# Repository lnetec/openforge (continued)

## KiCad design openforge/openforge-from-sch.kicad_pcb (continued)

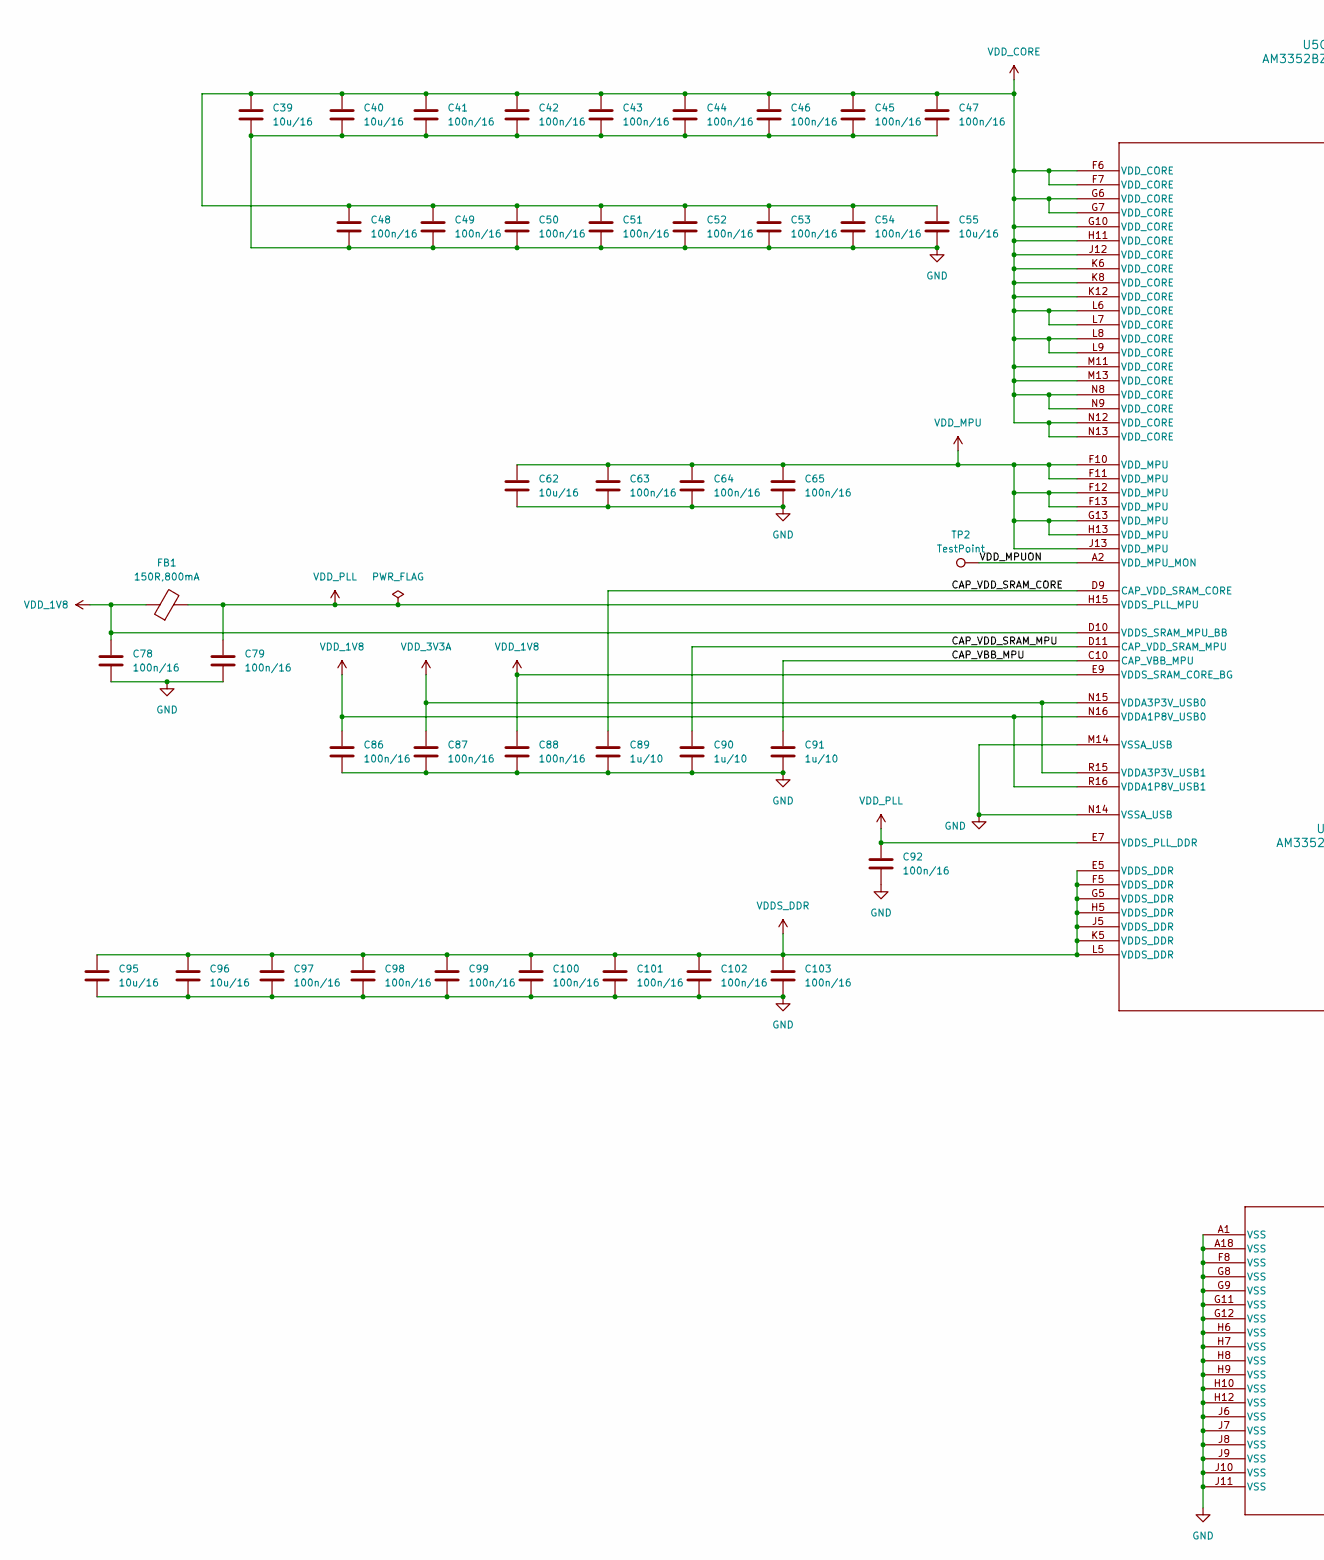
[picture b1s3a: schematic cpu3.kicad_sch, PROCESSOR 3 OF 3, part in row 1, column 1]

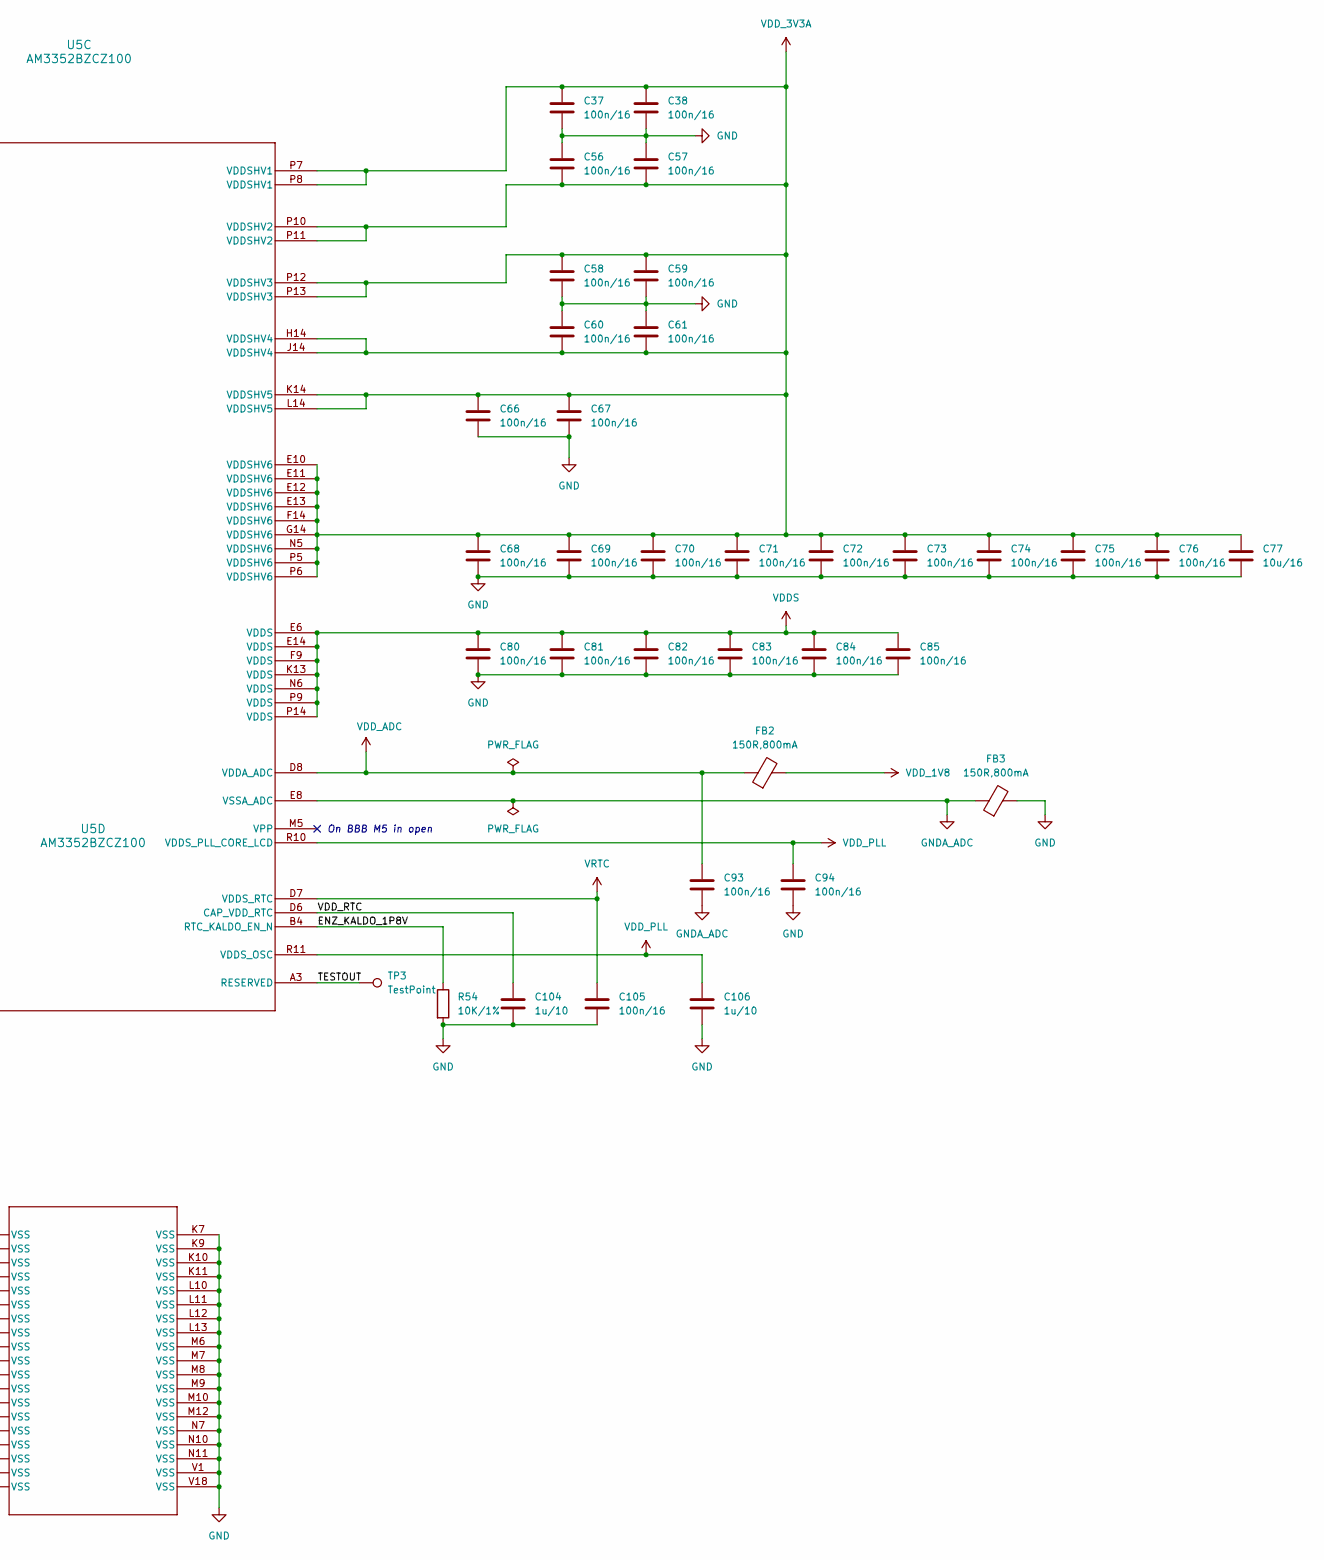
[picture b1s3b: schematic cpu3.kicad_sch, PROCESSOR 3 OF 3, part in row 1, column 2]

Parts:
C37, C38, C41, C42, C43, C44, C45, C46, C47, C48, C49, C50, C51, C52, C53, C54, C56, C57, C58, C59, C60, C61, C63, C64, C65, C66, C67, C68, C69, C70, C71, C72, C73, C74, C75, C76, C78, C79, C80, C81, C82, C83, C84, C85, C86, C87, C88, C92, C93, C94, C97, C98, C99, C100, C101, C102, C103, C105: 100n/16; C_0402_1005Metric
C39, C40, C55, C62, C95, C96: 10u/16; C_0805_2012Metric
C77: 10u/16; C_0402_1005Metric
C89, C90, C91, C104, C106: 1u/10; C_0402_1005Metric
FB1, FB2, FB3: 150R,800mA; L_0805_2012Metric
R54: 10K/1%; R_0402_1005Metric
TP2, TP3: TestPoint; TestPoint_Pad_1.5x1.5mm
U5: AM3352BZCZ100; ZCZ0324A

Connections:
/CPU3/CAP_VBB_MPU: C91.1, U5.C10 (CAP_VBB_MPU)
/CPU3/CAP_VDD_SRAM_CORE: C89.1, U5.D9 (CAP_VDD_SRAM_CORE)
/CPU3/CAP_VDD_SRAM_MPU: C90.1, U5.D11 (CAP_VDD_SRAM_MPU)
/CPU3/ENZ_KALDO_1P8V: R54.1, U5.B4 (RTC_KALDO_EN_N)
/CPU3/TESTOUT: TP3.1, U5.A3 (RESERVED)
/CPU3/VDD_MPUON: TP2.1, U5.A2 (VDD_MPU_MON)
/CPU3/VDD_RTC: C104.1, U5.D6 (CAP_VDD_RTC)
GND: C37.2, C38.2, C39.2, C40.2, C41.2, C42.2, C43.2, C44.2, C45.2, C46.2, C47.2, C48.2, C49.2, C50.2, C51.2, C52.2, C53.2, C54.2, C55.2, C56.1, C57.1, C58.2, C59.2, C60.1, C61.1, C62.2, C63.2, C64.2, C65.2, C66.2, C67.2, C68.2, C69.2, C70.2, C71.2, C72.2, C73.2, C74.2, C75.2, C76.2, C77.2, C78.2, C79.2, C80.2, C81.2, C82.2, C83.2, C84.2, C85.2, C86.2, C87.2, C88.2, C89.2, C90.2, C91.2, C92.2, C94.2, C95.2, C96.2, C97.2, C98.2, C99.2, C100.2, C101.2, C102.2, C103.2, C104.2, C105.2, C106.2, FB3.2, R54.2, U5.A1 (VSS), U5.A18 (VSS), U5.F8 (VSS), U5.G8 (VSS), U5.G9 (VSS), U5.G11 (VSS), U5.G12 (VSS), U5.H6 (VSS), U5.H7 (VSS), U5.H8 (VSS), U5.H9 (VSS), U5.H10 (VSS), U5.H12 (VSS), U5.J6 (VSS), U5.J7 (VSS), U5.J8 (VSS), U5.J9 (VSS), U5.J10 (VSS), U5.J11 (VSS), U5.K7 (VSS), U5.K9 (VSS), U5.K10 (VSS), U5.K11 (VSS), U5.L10 (VSS), U5.L11 (VSS), U5.L12 (VSS), U5.L13 (VSS), U5.M6 (VSS), U5.M7 (VSS), U5.M8 (VSS), U5.M9 (VSS), U5.M10 (VSS), U5.M12 (VSS), U5.M14 (VSSA_USB), U5.N7 (VSS), U5.N10 (VSS), U5.N11 (VSS), U5.N14 (VSSA_USB), U5.V1 (VSS), U5.V18 (VSS); also elsewhere on the board
GNDA_ADC: C93.2, FB3.1, U5.E8 (VSSA_ADC); also elsewhere on the board
VDDS: C80.1, C81.1, C82.1, C83.1, C84.1, C85.1, U5.E6 (VDDS), U5.E14 (VDDS), U5.F9 (VDDS), U5.K13 (VDDS), U5.N6 (VDDS), U5.P9 (VDDS), U5.P14 (VDDS); also elsewhere on the board
VDDS_DDR: C95.1, C96.1, C97.1, C98.1, C99.1, C100.1, C101.1, C102.1, C103.1, U5.E5 (VDDS_DDR), U5.F5 (VDDS_DDR), U5.G5 (VDDS_DDR), U5.H5 (VDDS_DDR), U5.J5 (VDDS_DDR), U5.K5 (VDDS_DDR), U5.L5 (VDDS_DDR); also elsewhere on the board
VDD_1V8: C78.1, C86.1, C88.1, FB1.1, FB2.2, U5.D10 (VDDS_SRAM_MPU_BB), U5.E9 (VDDS_SRAM_CORE_BG), U5.N16 (VDDA1P8V_USB0), U5.R16 (VDDA1P8V_USB1); also elsewhere on the board
VDD_3V3A: C37.1, C38.1, C56.2, C57.2, C58.1, C59.1, C60.2, C61.2, C66.1, C67.1, C68.1, C69.1, C70.1, C71.1, C72.1, C73.1, C74.1, C75.1, C76.1, C77.1, C87.1, U5.E10 (VDDSHV6), U5.E11 (VDDSHV6), U5.E12 (VDDSHV6), U5.E13 (VDDSHV6), U5.F14 (VDDSHV6), U5.G14 (VDDSHV6), U5.H14 (VDDSHV4), U5.J14 (VDDSHV4), U5.K14 (VDDSHV5), U5.L14 (VDDSHV5), U5.N5 (VDDSHV6), U5.N15 (VDDA3P3V_USB0), U5.P5 (VDDSHV6), U5.P6 (VDDSHV6), U5.P7 (VDDSHV1), U5.P8 (VDDSHV1), U5.P10 (VDDSHV2), U5.P11 (VDDSHV2), U5.P12 (VDDSHV3), U5.P13 (VDDSHV3), U5.R15 (VDDA3P3V_USB1); also elsewhere on the board
VDD_ADC: C93.1, FB2.1, U5.D8 (VDDA_ADC); also elsewhere on the board
VDD_CORE: C39.1, C40.1, C41.1, C42.1, C43.1, C44.1, C45.1, C46.1, C47.1, C48.1, C49.1, C50.1, C51.1, C52.1, C53.1, C54.1, C55.1, U5.F6 (VDD_CORE), U5.F7 (VDD_CORE), U5.G6 (VDD_CORE), U5.G7 (VDD_CORE), U5.G10 (VDD_CORE), U5.H11 (VDD_CORE), U5.J12 (VDD_CORE), U5.K6 (VDD_CORE), U5.K8 (VDD_CORE), U5.K12 (VDD_CORE), U5.L6 (VDD_CORE), U5.L7 (VDD_CORE), U5.L8 (VDD_CORE), U5.L9 (VDD_CORE), U5.M11 (VDD_CORE), U5.M13 (VDD_CORE), U5.N8 (VDD_CORE), U5.N9 (VDD_CORE), U5.N12 (VDD_CORE), U5.N13 (VDD_CORE); also elsewhere on the board
VDD_MPU: C62.1, C63.1, C64.1, C65.1, U5.F10 (VDD_MPU), U5.F11 (VDD_MPU), U5.F12 (VDD_MPU), U5.F13 (VDD_MPU), U5.G13 (VDD_MPU), U5.H13 (VDD_MPU), U5.J13 (VDD_MPU); also elsewhere on the board
VDD_PLL: C79.1, C92.1, C94.1, C106.1, FB1.2, U5.E7 (VDDS_PLL_DDR), U5.H15 (VDDS_PLL_MPU), U5.R10 (VDDS_PLL_CORE_LCD), U5.R11 (VDDS_OSC)
VRTC: C105.1, U5.D7 (VDDS_RTC); also elsewhere on the board

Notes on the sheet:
On BBB M5 in open

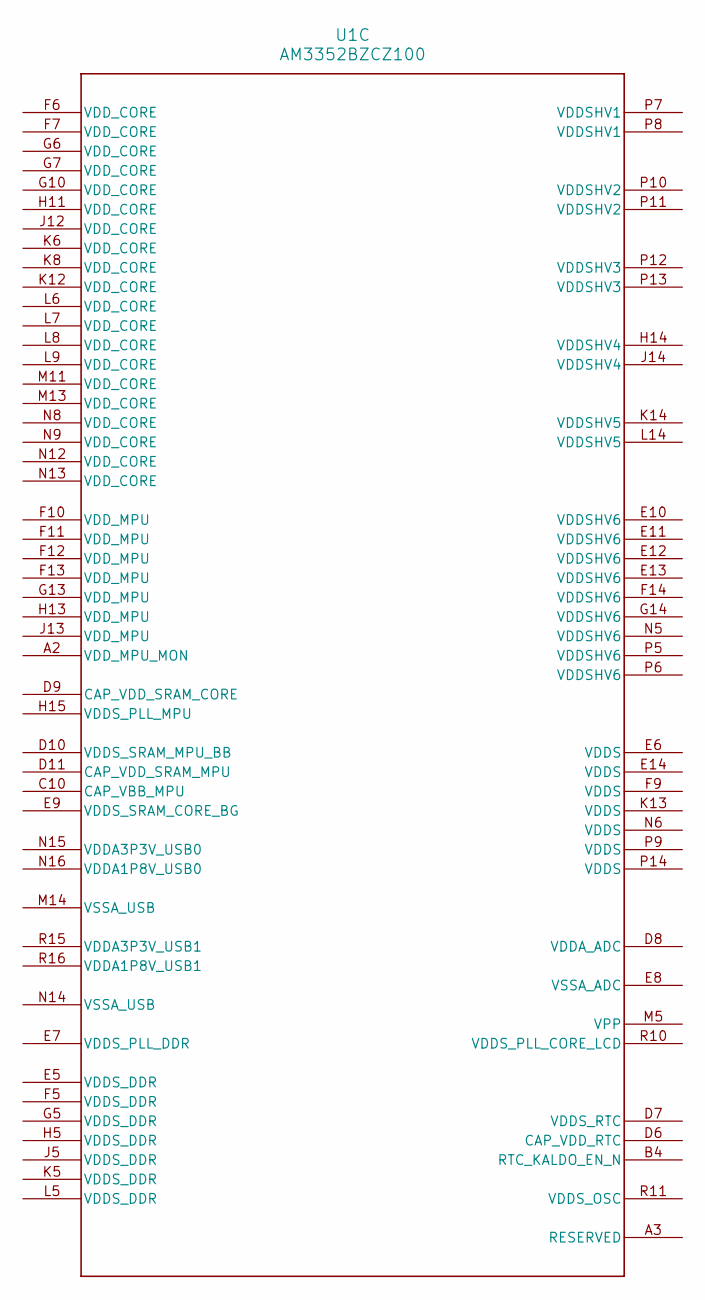
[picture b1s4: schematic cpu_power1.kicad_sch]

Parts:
U1: AM3352BZCZ100; ZCZ0324A

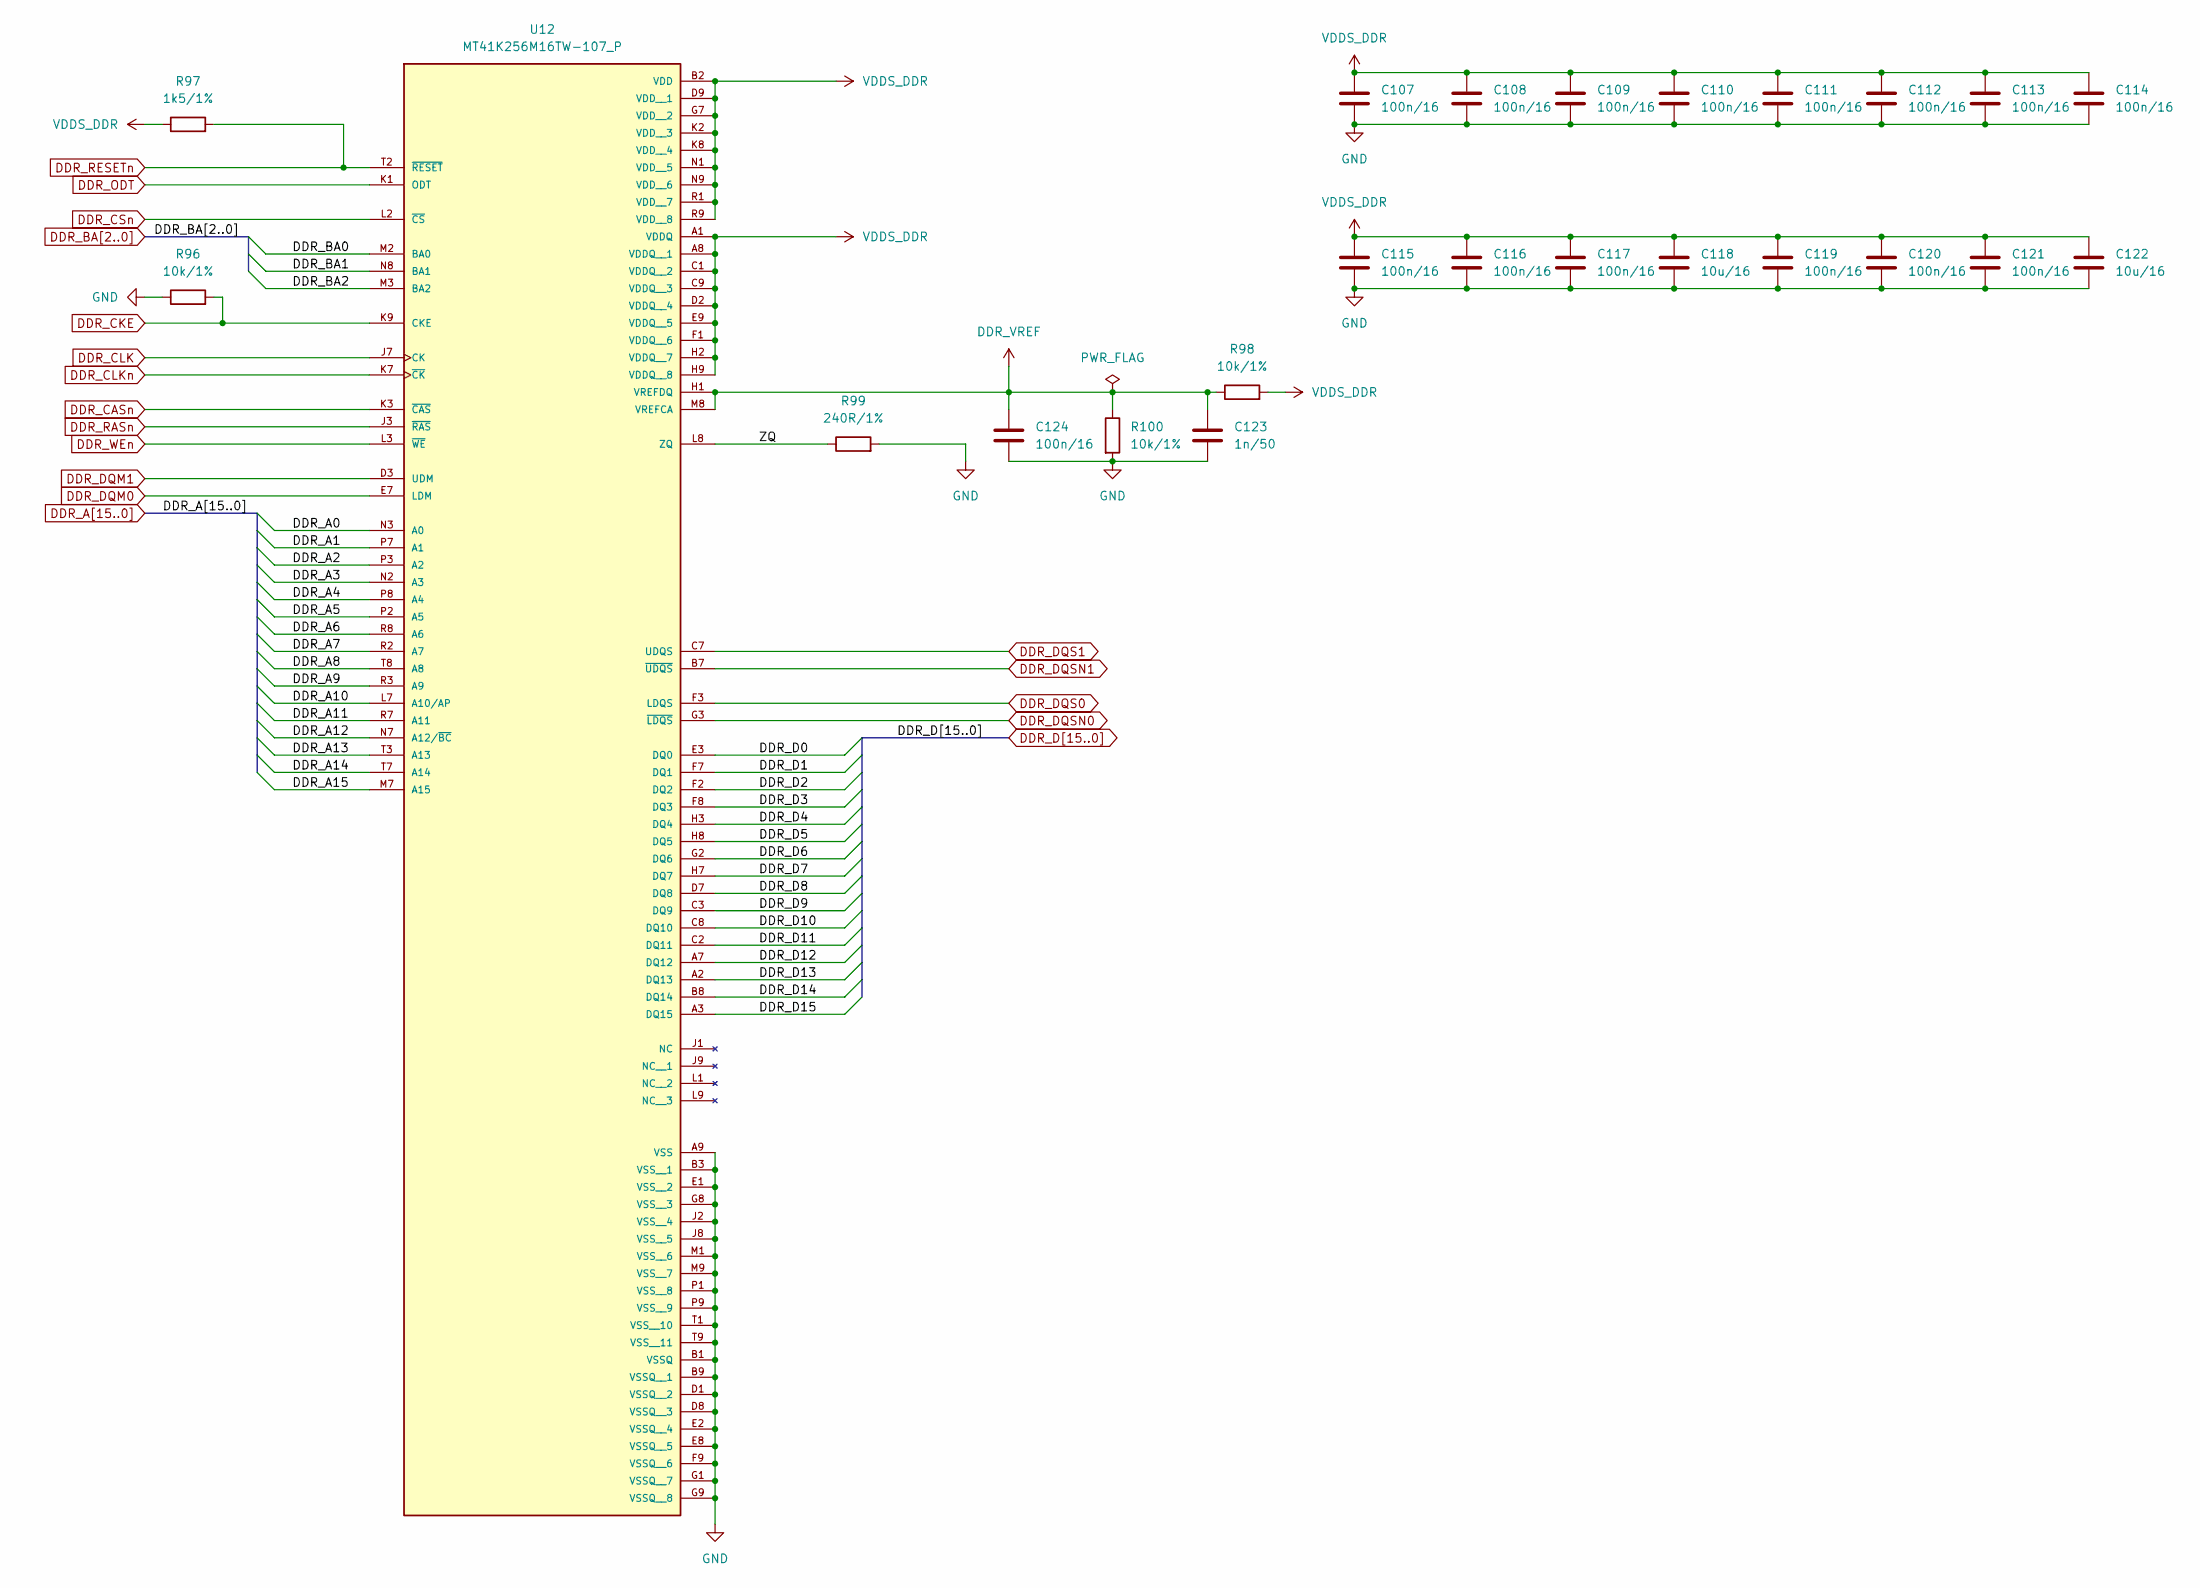
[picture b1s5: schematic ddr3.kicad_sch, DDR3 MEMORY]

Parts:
C107, C108, C109, C110, C111, C112, C113, C114, C115, C116, C117, C119, C120, C121, C124: 100n/16; C_0402_1005Metric
C118, C122: 10u/16; C_0805_2012Metric
C123: 1n/50; C_0402_1005Metric
R96, R98, R100: 10k/1%; R_0402_1005Metric
R97: 1k5/1%; R_0402_1005Metric
R99: 240R/1%; R_0402_1005Metric
U12: MT41K256M16TW-107_P; BGA96C80P9X16_1400X800X120; PARTREV P

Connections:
/DDR3 Memory/ZQ: R99.1, U12.L8 (ZQ)
DDR_A0: U12.N3 (A0); also elsewhere on the board
DDR_A1: U12.P7 (A1); also elsewhere on the board
DDR_A2: U12.P3 (A2); also elsewhere on the board
DDR_A3: U12.N2 (A3); also elsewhere on the board
DDR_A4: U12.P8 (A4); also elsewhere on the board
DDR_A5: U12.P2 (A5); also elsewhere on the board
DDR_A6: U12.R8 (A6); also elsewhere on the board
DDR_A7: U12.R2 (A7); also elsewhere on the board
DDR_A8: U12.T8 (A8); also elsewhere on the board
DDR_A9: U12.R3 (A9); also elsewhere on the board
DDR_A10: U12.L7 (A10/AP); also elsewhere on the board
DDR_A11: U12.R7 (A11); also elsewhere on the board
DDR_A12: U12.N7 (A12/~BC); also elsewhere on the board
DDR_A13: U12.T3 (A13); also elsewhere on the board
DDR_A14: U12.T7 (A14); also elsewhere on the board
DDR_A15: U12.M7 (A15); also elsewhere on the board
DDR_BA0: U12.M2 (BA0); also elsewhere on the board
DDR_BA1: U12.N8 (BA1); also elsewhere on the board
DDR_BA2: U12.M3 (BA2); also elsewhere on the board
DDR_CASn: U12.K3 (~CAS); also elsewhere on the board
DDR_CKE: R96.2, U12.K9 (CKE); also elsewhere on the board
DDR_CLK: U12.J7 (CK); also elsewhere on the board
DDR_CLKn: U12.K7 (~CK); also elsewhere on the board
DDR_CSn: U12.L2 (~CS); also elsewhere on the board
DDR_D0: U12.E3 (DQ0); also elsewhere on the board
DDR_D1: U12.F7 (DQ1); also elsewhere on the board
DDR_D2: U12.F2 (DQ2); also elsewhere on the board
DDR_D3: U12.F8 (DQ3); also elsewhere on the board
DDR_D4: U12.H3 (DQ4); also elsewhere on the board
DDR_D5: U12.H8 (DQ5); also elsewhere on the board
DDR_D6: U12.G2 (DQ6); also elsewhere on the board
DDR_D7: U12.H7 (DQ7); also elsewhere on the board
DDR_D8: U12.D7 (DQ8); also elsewhere on the board
DDR_D9: U12.C3 (DQ9); also elsewhere on the board
DDR_D10: U12.C8 (DQ10); also elsewhere on the board
DDR_D11: U12.C2 (DQ11); also elsewhere on the board
DDR_D12: U12.A7 (DQ12); also elsewhere on the board
DDR_D13: U12.A2 (DQ13); also elsewhere on the board
DDR_D14: U12.B8 (DQ14); also elsewhere on the board
DDR_D15: U12.A3 (DQ15); also elsewhere on the board
DDR_DQM0: U12.E7 (LDM); also elsewhere on the board
DDR_DQM1: U12.D3 (UDM); also elsewhere on the board
DDR_DQS0: U12.F3 (LDQS); also elsewhere on the board
DDR_DQS1: U12.C7 (UDQS); also elsewhere on the board
DDR_DQSN0: U12.G3 (~LDQS); also elsewhere on the board
DDR_DQSN1: U12.B7 (~UDQS); also elsewhere on the board
DDR_ODT: U12.K1 (ODT); also elsewhere on the board
DDR_RASn: U12.J3 (~RAS); also elsewhere on the board
DDR_RESETn: R97.2, U12.T2 (~RESET); also elsewhere on the board
DDR_VREF: C123.1, C124.1, R98.1, R100.1, U12.H1 (VREFDQ), U12.M8 (VREFCA); also elsewhere on the board
DDR_WEn: U12.L3 (~WE); also elsewhere on the board
GND: C107.2, C108.2, C109.2, C110.2, C111.2, C112.2, C113.2, C114.2, C115.2, C116.2, C117.2, C118.2, C119.2, C120.2, C121.2, C122.2, C123.2, C124.2, R96.1, R99.2, R100.2, U12.A9 (VSS), U12.B1 (VSSQ), U12.B3 (VSS__1), U12.B9 (VSSQ__1), U12.D1 (VSSQ__2), U12.D8 (VSSQ__3), U12.E1 (VSS__2), U12.E2 (VSSQ__4), U12.E8 (VSSQ__5), U12.F9 (VSSQ__6), U12.G1 (VSSQ__7), U12.G8 (VSS__3), U12.G9 (VSSQ__8), U12.J2 (VSS__4), U12.J8 (VSS__5), U12.M1 (VSS__6), U12.M9 (VSS__7), U12.P1 (VSS__8), U12.P9 (VSS__9), U12.T1 (VSS__10), U12.T9 (VSS__11); also elsewhere on the board
VDDS_DDR: C107.1, C108.1, C109.1, C110.1, C111.1, C112.1, C113.1, C114.1, C115.1, C116.1, C117.1, C118.1, C119.1, C120.1, C121.1, C122.1, R97.1, R98.2, U12.A1 (VDDQ), U12.A8 (VDDQ__1), U12.B2 (VDD), U12.C1 (VDDQ__2), U12.C9 (VDDQ__3), U12.D2 (VDDQ__4), U12.D9 (VDD__1), U12.E9 (VDDQ__5), U12.F1 (VDDQ__6), U12.G7 (VDD__2), U12.H2 (VDDQ__7), U12.H9 (VDDQ__8), U12.K2 (VDD__3), U12.K8 (VDD__4), U12.N1 (VDD__5), U12.N9 (VDD__6), U12.R1 (VDD__7), U12.R9 (VDD__8); also elsewhere on the board

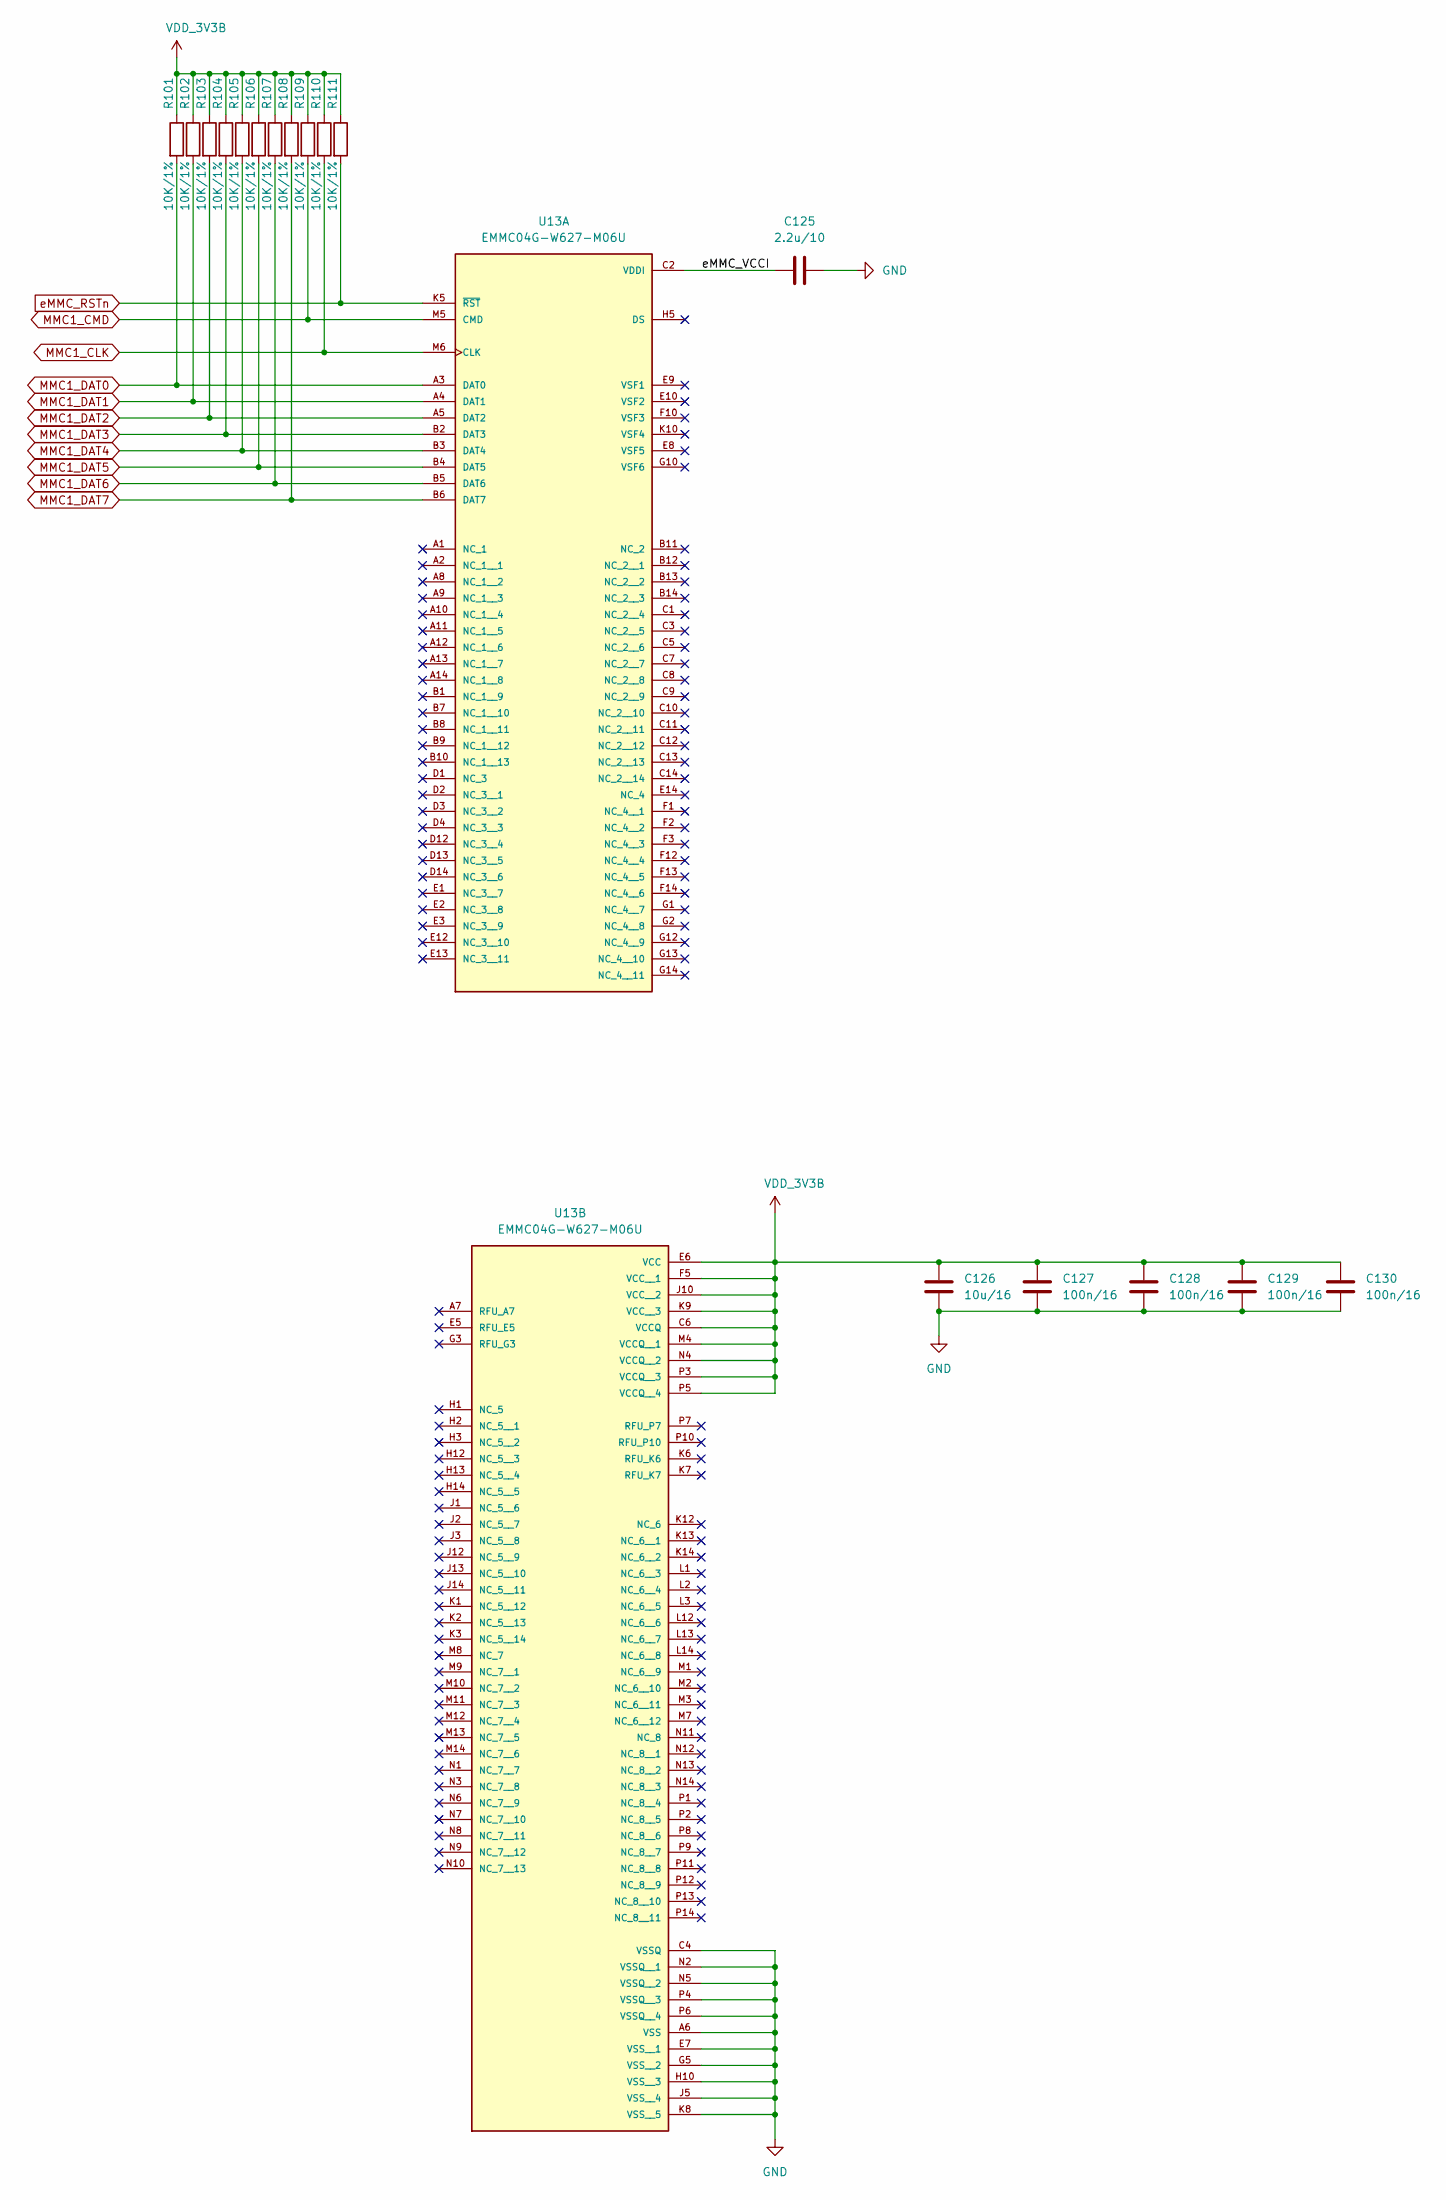
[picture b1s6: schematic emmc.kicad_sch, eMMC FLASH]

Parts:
C125: 2.2u/10; C_0402_1005Metric
C126: 10u/16; C_0805_2012Metric
C127, C128, C129, C130: 100n/16; C_0402_1005Metric
R101, R102, R103, R104, R105, R106, R107, R108, R109, R110, R111: 10K/1%; R_0402_1005Metric
U13: EMMC04G-W627-M06U; BGA153N50P14X14_1300X1150X100N

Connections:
/eMMC/eMMC_VCCI: C125.1, U13.C2 (VDDI)
GND: C125.2, C126.2, C127.2, C128.2, C129.2, C130.2, U13.A6 (VSS), U13.C4 (VSSQ), U13.E7 (VSS__1), U13.G5 (VSS__2), U13.H10 (VSS__3), U13.J5 (VSS__4), U13.K8 (VSS__5), U13.N2 (VSSQ__1), U13.N5 (VSSQ__2), U13.P4 (VSSQ__3), U13.P6 (VSSQ__4); also elsewhere on the board
MMC1_CLK: R110.2, U13.M6 (CLK); also elsewhere on the board
MMC1_CMD: R109.2, U13.M5 (CMD); also elsewhere on the board
MMC1_DAT0: R101.2, U13.A3 (DAT0); also elsewhere on the board
MMC1_DAT1: R102.2, U13.A4 (DAT1); also elsewhere on the board
MMC1_DAT2: R103.2, U13.A5 (DAT2); also elsewhere on the board
MMC1_DAT3: R104.2, U13.B2 (DAT3); also elsewhere on the board
MMC1_DAT4: R105.2, U13.B3 (DAT4); also elsewhere on the board
MMC1_DAT5: R106.2, U13.B4 (DAT5); also elsewhere on the board
MMC1_DAT6: R107.2, U13.B5 (DAT6); also elsewhere on the board
MMC1_DAT7: R108.2, U13.B6 (DAT7); also elsewhere on the board
VDD_3V3B: C126.1, C127.1, C128.1, C129.1, C130.1, R101.1, R102.1, R103.1, R104.1, R105.1, R106.1, R107.1, R108.1, R109.1, R110.1, R111.1, U13.C6 (VCCQ), U13.E6 (VCC), U13.F5 (VCC__1), U13.J10 (VCC__2), U13.K9 (VCC__3), U13.M4 (VCCQ__1), U13.N4 (VCCQ__2), U13.P3 (VCCQ__3), U13.P5 (VCCQ__4); also elsewhere on the board
eMMC_RSTn: R111.2, U13.K5 (~RST); also elsewhere on the board
